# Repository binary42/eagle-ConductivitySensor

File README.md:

# eagle-ConductivitySensor
Schematic and Board Layout - Eagle CAD

Additional Comments about Any Warranty:

There is none. Zero. Check everything about this circuit design before you power on anything. If you zap a controller or yourself, that's on you.

Design Notes:

Usage Notes:

TBA

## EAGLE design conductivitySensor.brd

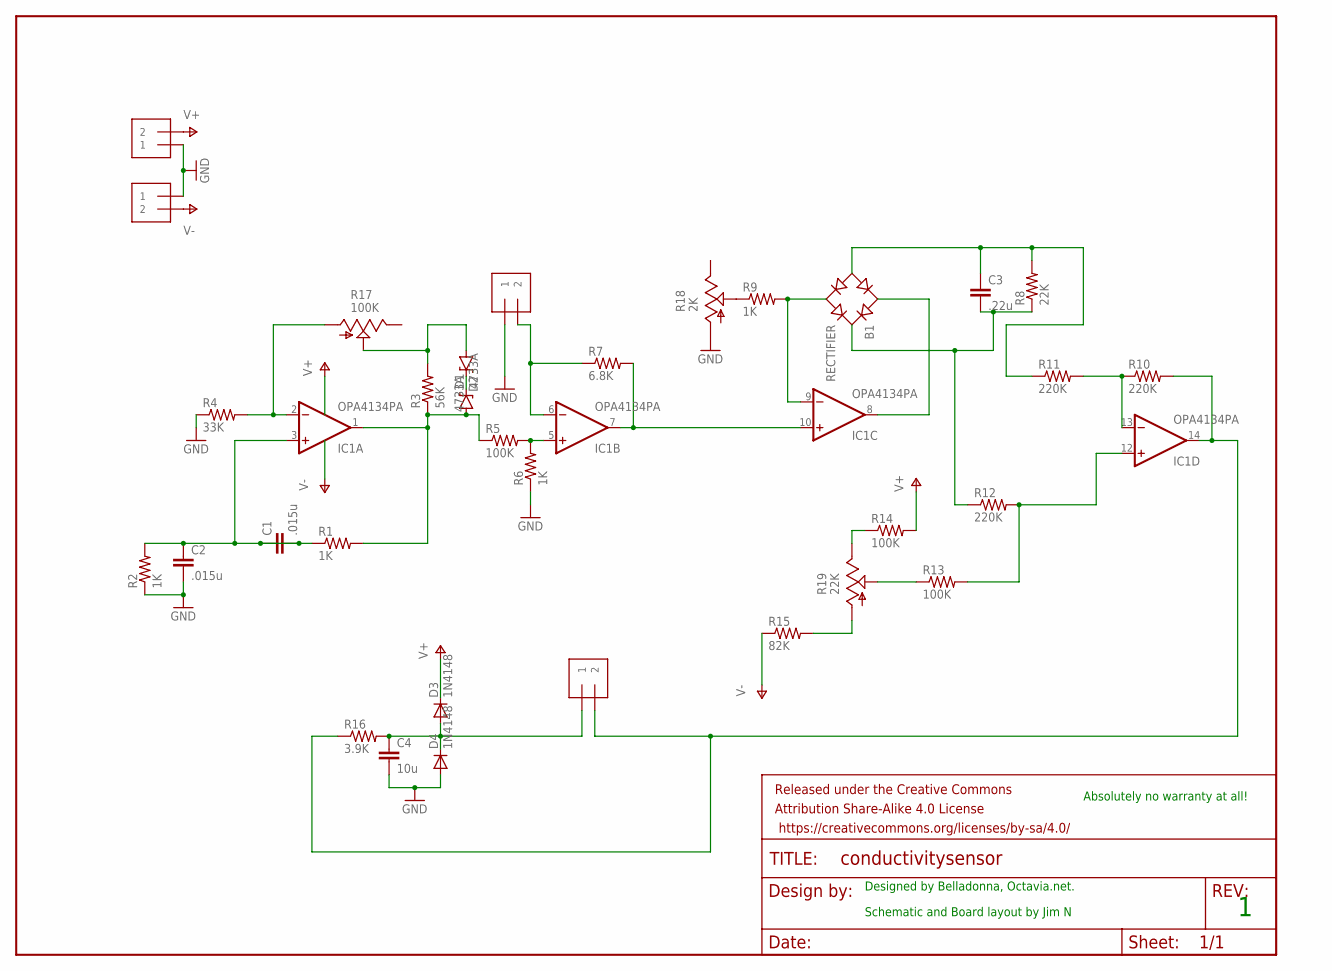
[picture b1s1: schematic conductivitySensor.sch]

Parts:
B1: RECTIFIER; DSI32A
C1, C2: .015u; CAP-PTH-SMALL
C3: .22u; CAP-PTH-SMALL
C4: 10u; CAP-PTH-SMALL
D1, D2: 4733A; DIODE-ZENER
D3, D4: 1N4148; DO35-7
FRAME1: FRAME-LETTER; CREATIVE_COMMONS
IC1: OPA4134PA; DIL14
J1, J2: 1X2-3.5MM
J3: A/D out Pin1 EC out P2; 1X2-3.5MM
J4: 1X2-3.5MM - Probe Connection; 1X2-3.5MM
R1, R2, R6, R9: 1K; AXIAL-0.3
R3: 56K; AXIAL-0.3
R4: 33K; AXIAL-0.3
R5, R13, R14: 100K; AXIAL-0.3
R7: 6.8K; AXIAL-0.3
R8: 22K; AXIAL-0.3
R10, R11, R12: 220K; AXIAL-0.3
R15: 82K; AXIAL-0.3
R16: 3.9K; AXIAL-0.3
R17: 100K; CA6V
R18: 2K; CA6V
R19: 22K; CA6V

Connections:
GND: C2.2, C4.2, D4.A, J1.1, J2.1, J4.1, R2.P$1 (1), R4.P$1 (1), R6.P$1 (1), R18.A
unnamed: C1.1, C1.2, C2.1, IC1.3 (+IN), R1.P$1 (1), R2.P$2 (2)
unnamed: D1.P$1 (C), D2.P$1 (C)
unnamed: IC1.2 (-IN), R4.P$2 (2), R17.A
unnamed: D1.P$2 (A), IC1.1 (OUT), R1.P$2 (2), R3.P$1 (1), R5.P$1 (1)
unnamed: R9.P$1 (1), R18.S
unnamed: IC1.7 (OUT), IC1.10 (+IN), R7.P$2 (2)
unnamed: IC1.6 (-IN), J4.2, R7.P$1 (1)
unnamed: IC1.5 (+IN), R5.P$2 (2), R6.P$2 (2)
unnamed: B1.AC2, IC1.9 (-IN), R9.P$2 (2)
unnamed: B1.AC1, IC1.8 (OUT)
unnamed: C4.1, D3.A, D4.C, J3.1, R16.P$2 (2)
unnamed: D2.P$2 (A), R3.P$2 (2), R17.S
unnamed: R15.P$2 (2), R19.A
unnamed: R14.P$1 (1), R19.E
unnamed: R13.P$1 (1), R19.S
unnamed: IC1.12 (+IN), R12.P$2 (2), R13.P$2 (2)
unnamed: IC1.14 (OUT), J3.2, R10.P$2 (2), R16.P$1 (1)
unnamed: IC1.13 (-IN), R10.P$1 (1), R11.P$2 (2)
unnamed: B1.+, C3.2, R8.P$1 (1), R12.P$1 (1)
unnamed: B1.-, C3.1, R8.P$2 (2), R11.P$1 (1)
V+: D3.C, IC1.4 (V+), J1.2, R14.P$2 (2)
V-: IC1.11 (V-), J2.2, R15.P$1 (1)

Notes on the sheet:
Designed by Belladonna, Octavia.net.
Schematic and Board layout by Jim N
Absolutely no warranty at all!

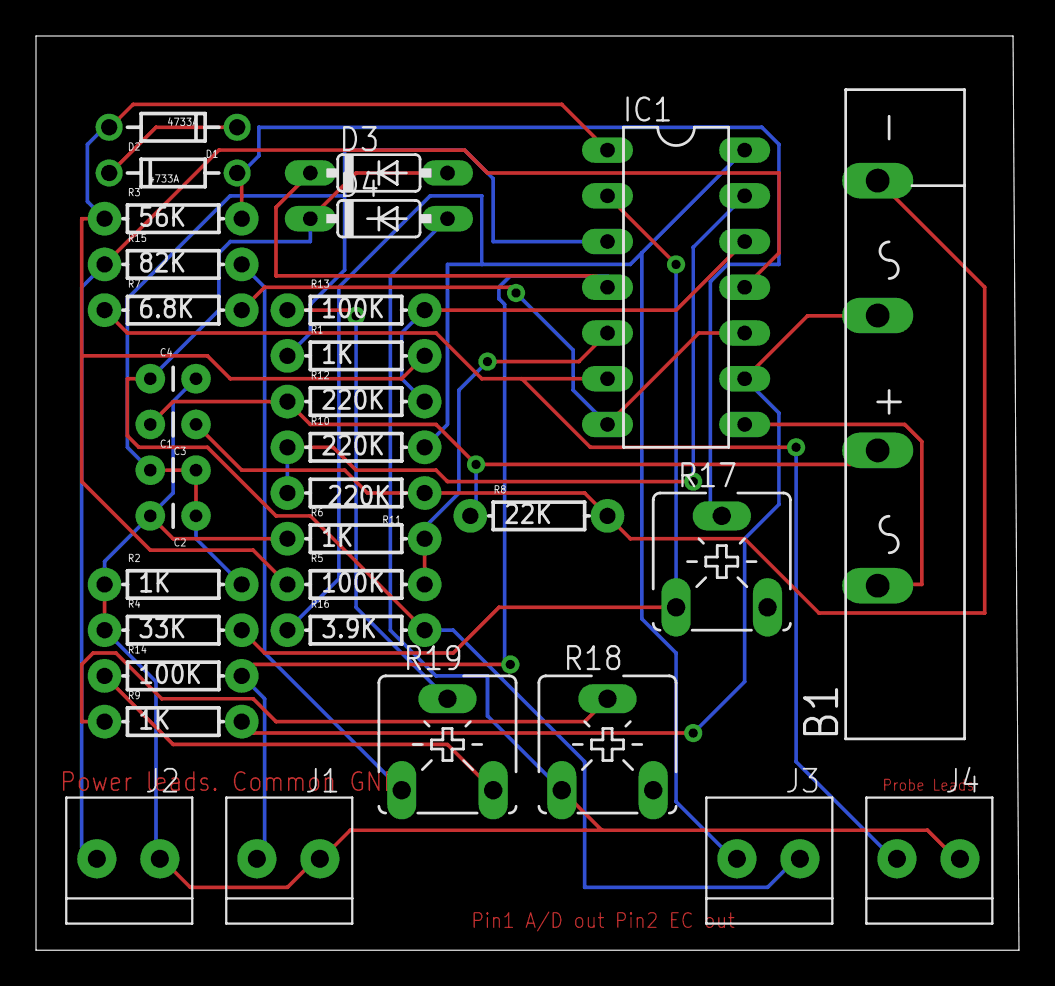
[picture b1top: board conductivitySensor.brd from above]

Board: 2 copper layers, 54.6 x 50.8 mm, 34 parts (0 on the bottom side), 23 nets.

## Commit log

2015-08-15 init commit
2015-08-15 additions to read.me

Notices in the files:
parts and their libraries:
SparkFun-Passives: Licensing: Creative Commons ShareAlike 4.0 International - https://creativecommons.org/licenses/by-sa/4.0
SparkFun-Aesthetics: Released under the Creative Commons Attribution Share-Alike 4.0 License
SparkFun-Aesthetics: https://creativecommons.org/licenses/by-sa/4.0
